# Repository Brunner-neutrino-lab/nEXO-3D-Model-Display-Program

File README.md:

# nEXO 3D Model and Display

## Overview

This project showcases a scaled-down, 3D-printed model of the nEXO detector, designed to visualize various data related to muon interactions and double beta decay events. The model is created using SolidWorks and powered by a Raspberry Pi, enabling interactive LED displays and simulated data visualization. This project aims to present condensed data from ten years of observation, highlighting the rarity of neutrino-less double beta decay.

## Table of Contents

1. [Introduction](#introduction)
2. [Project Features](#project-features)
3. [Responsibilities](#responsibilities)
4. [Hardware Components](#hardware-components)
5. [Software Components](#software-components)
6. [Setup and Installation](#setup-and-installation)
7. [Data Simulation](#data-simulation)
8. [Usage](#usage)
9. [Acknowledgments](#acknowledgments)

## Introduction

The nEXO detector is part of an experiment projected to detect neutrino-less double beta decay. Our project involves creating a scaled-down 3D model of the detector to visualize simulated muon data and rare decay events in an engaging and informative manner.

## Project Features

- **True-to-Scale 3D Model**: Created in SolidWorks, scaled down by a factor of 100, and optimized for 3D printing.
- **Simulated Data Visualization**:
  - Muons passing through the TPC (Time Projection Chamber).
  - Muons passing through the outer detector.
  - Coincident muons passing through both the TPC and outer detector.
  - Background Region of Interest (ROI) data.
  - Xenon 137 data.
  - Estimated rate of neutrino-less double beta decay.
- **Interactive LED Display**: Powered by a Raspberry Pi, the LED display will showcase multiple half-lives of the decay to highlight its rarity.
- **Condensed Time Frame**: Displaying ten years or five years of data in a two-minute or one-minute visualization respectively.

## Responsibilities

1. 3D model and printing
- Grace, Felix
2. Hardware
- Julien, Felix 
3. Programming
- Sophie, Emilio, Eliot

Brian is advising the programming and hardware

## Hardware Components

- Raspberry Pi (User: pi,  Pass: Element54$)
- 3D-printed model of the nEXO detector (32 components)
- LEDs (5 blue for walls and 4 blue for floor, RGB for TPC)
- Power supply
- Current-limiting resistors
- IC (transistors)
- HAT for raspberry pi
- Wires (mainly used 26AWG)
- Glue
- Mirror sheet

## Software Components

- SolidWorks for 3D modeling
- Python for controlling the Raspberry Pi and LEDs
- Data from previous simulation scripts for muon and decay events

## Setup and Installation

1. **3D Printing**:
   - Use the SolidWorks files provided in the [sharepoint](https://mcgill.sharepoint.com/:f:/s/BrunnerNeutrinoLabModels_Group/EvGFXZofQUZPt6qD_oMlr6YBIfcuM76ZlL9AQwnTyHu-Tg?e=94aHd1) to print the scaled-down model of the nEXO detector.
   
2. **Hardware Assembly**:
   - Schematics for the Raspberry Pi HAT and inside the model are found in the 'Schematics' folder.
   - Full tutorial on how to asssemble your own HAT found in 'nEXO Scale Model HAT text.docx'

4. **Software Installation**:
  - Assignment of GPIO pins for LEDS:
      - wallGPIO = 17 #physical/board pin 11
      - floorGPIO = 27 #physical/board pin 13
      - redGPIO = 9 #physical/board pin 21
      - greenGPIO = 11 #physical/board pin 23
      - blueGPIO = 25 #physical/board pin 22
  - The program to display the LEDs is found in the file 'LED_program.py'
  - 'Test.py' was only used to store the RGB values for the TPC colours.
      - in the 'Schematic' folder the LED colour assignment to events is found.

## Data Simulation
General approach: calculate the mean/expected time between events (for our time scale of 2 min = 10 years), then randomly sample the time between LED flashes using an exponential distribution (distribution for time between Poisson events). We have the option
 to vary the half-life of 0vbb as well as the LXe volume (inner 2t or inner 1t). 

The TPC will be flashed different colours for 5 different events in the ROI (the ROI is SS events, with energy within 0vbb FHWM): 
  - 0vbb
  - 2vbb
  - solar v
  - Xe-137 activations
  - and the remaining background events. 

0vbb: Mean number of decays per year is calculated based on the mean lifetime (half-life divided by log(2)), assuming 76.1% of events are in the ROI (as FHWM is approximately 76.1% of area under Gaussian distribution). 

  - 3 sigma discovery potential half-life: 7.4 x 10^27 years (https://iopscience.iop.org/article/10.1088/1361-6471/ac3631/pdf)   
  - Half-life sensitivity: 1.35 × 10^28 years
  - Our third option is currently 1 x 10^27 years.

Total background rate (https://arxiv.org/abs/1805.11142v2, table 3.1):  
  - Inner 2 tons: 3.6 × 10^−4 events/(FWHM·kg·yr)  
  - Inner 1 ton: 1.4 × 10^−4 events/(FWHM·kg·yr)  

Events in the background are separated into 2vbb, solar v, Xe-137 and remaining background according to the composition within FWHM for the inner 2t (https://iopscience.iop.org/article/10.1088/1361-6471/ac3631/pdf, estimated from Fig. 8):  
  - 2vbb: 0.8%  
  - Solar v: 2.1%  
  - Xe-137: 2.4%   
  - Rest of background: 94.7%  

The outer detector (walls and floor) will be flashed for muons (these rates may have to be scaled differently as they are very high with our time scale; currently the lights just stay on):  
  - Muons through TPC: about 0.6 per day 
  - Muons through outer cryostat: about 5 per day 

## Usage

1. **Start the Visualization**:
   - Run the main control script: GUI_program_with_LEDs.py
   - GUI will allow the user to choose options before running simulation

2. **Interacting with the Model**:
   - The LEDs will display different data sets including muons, 2vbb, 0vbb, ROI background data, and Xenon 137 data.
   - There will be an option to view the data from the inner 1 tonne as well as the inner 2 tonne of the detector.
   - Observe the visualization of the estimated rate of neutrino-less double beta decay and its half-lives.
3. **Connecting over SSH**
   - pi must be connected to the same network as device (ethernet/internet)
   - type into terminal 'ssh pi@[pi IP address]'
   - if displaying on touchscreeen you have to define the display enviroment (the screen is just DISPLAY=:0) before the command
     - ex. DISPLAY=:0 gui.py
     - ex. sudo DISPLAY=:0 LEDs.py

## Acknowledgments

This project is developed for the nEXO collaboration's Director's Review.
For questions contact Grace at grace.champagne@mail.mcgill.ca

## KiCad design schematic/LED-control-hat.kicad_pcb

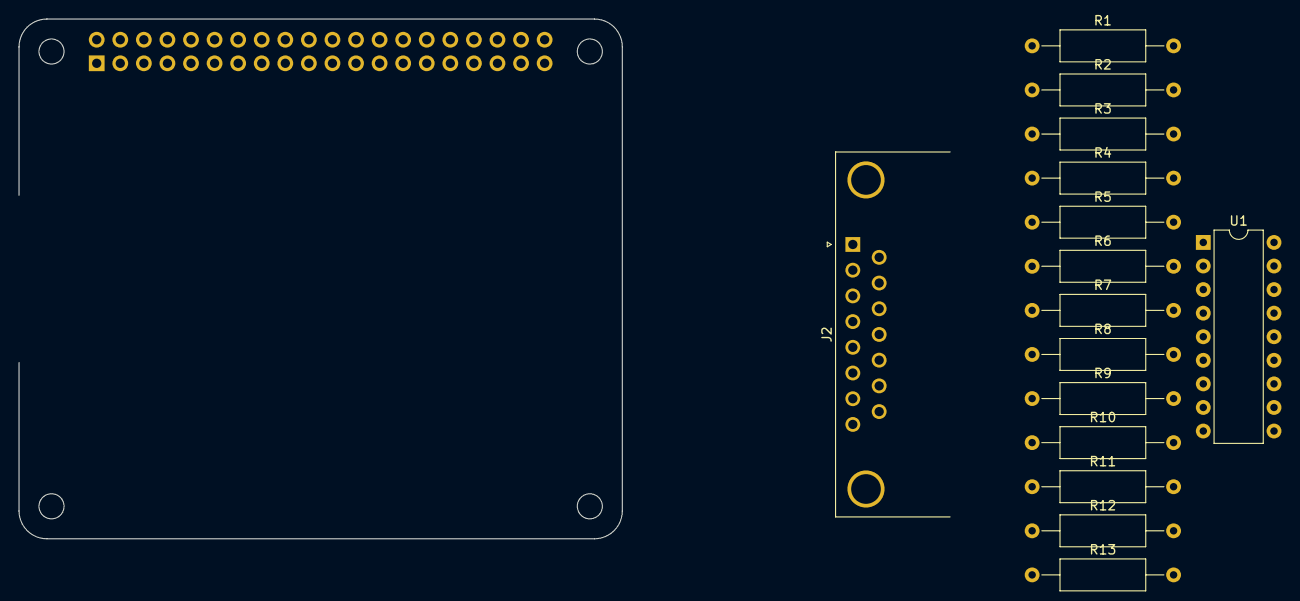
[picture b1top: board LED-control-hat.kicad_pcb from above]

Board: 2 copper layers, 65.0 x 56.0 mm, 20 parts (1 on the bottom side), 26 nets, no tracks yet.

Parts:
J1: GPIO; PinSocket_2x20_P2.54mm_Vertical
J2: DA15_Receptacle; DSUB-15_Female_Horizontal_P2.77x2.84mm_EdgePinOffset7.70mm_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
MH1, MH2, MH3, MH4: MountingHole_2.7mm_M2.5
R1, R2, R3, R4, R5, R6, R7, R8, R9, R10, R11, R12, R13: R_US; R_Axial_DIN0309_L9.0mm_D3.2mm_P15.24mm_Horizontal
U1: ULN2803A; DIP-18_W7.62mm

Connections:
+3V3: J1.1, J1.17
+5V: J1.2, J1.4, J2.1
/GPIO17: J1.11, U1.1 (I1)
/GPIO22: J1.15, U1.2 (I2)
/GPIO23: J1.16, U1.3 (I3)
/GPIO24: J1.18, U1.4 (I4)
/GPIO25: J1.22, U1.5 (I5)
GND: J1.6, J1.9, J1.14, J1.20, J1.25, J1.30, J1.34, J1.39, U1.9 (GND)
unnamed: J2.9, R1.2
unnamed: J2.10, R3.2
unnamed: J2.12, R7.2
unnamed: J2.13, R9.2
unnamed: J2.14, R11.2
unnamed: J2.15, R13.2
unnamed: J2.11 (P111), R5.2
unnamed: J2.2, R2.2
unnamed: J2.3, R4.2
unnamed: J2.4, R6.2
unnamed: J2.5, R8.2
unnamed: J2.6, R10.2
unnamed: J2.7, R12.2
unnamed: R1.1, U1.18 (O1)
unnamed: R2.1, U1.17 (O2)
unnamed: R3.1, U1.16 (O3)
unnamed: R4.1, R5.1, R6.1, R7.1, R8.1, U1.15 (O4)
unnamed: R9.1, R10.1, R11.1, R12.1, R13.1, U1.14 (O5)

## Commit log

2024-06-10 Create 2024-06-10.md
    meeting minutes for first meeting
2024-06-11 Create 2024-05-17.md
    layout for meeting 2
2024-06-17 LED draft code
    to test if LED's turn on through GPIO pins with expected resistor values
2024-06-20 Create screenshot
2024-06-20 kicad
    all kicad files for HAT circuit and inside model connections
2024-06-20 screenshot
2024-06-20 LED colour assignments
2024-06-25 Create to_do.md
    to do list as well as completed tasks
2024-06-26 changes to LED colours
2024-06-26 changed GPIO.cleanup location
2024-07-02 files for GUI on touchscreen
2024-07-08 Delete 3d model code for gui.py
    downloading new one with comments
2024-07-08 GUI program with LEDs with comments
2024-07-08 Update GUI program with LEDs.py
    no more tkvideo
2024-07-08 Update GUI program with LEDs.py
    uncommented GPIO parts
2024-07-08 Update GUI program with LEDs.py
    made font smaller
2024-07-10 Create schematic
2024-07-10 Screenshots of Schematic
2024-07-11 Update GUI program with LEDs.py
    stop works?
2024-07-12 Create log.txt
    for when program starts at boot
2024-07-12 changes so that will start at boot
2024-07-12 getting red of useless files
2024-07-12 Update GUI program with LEDs.py
    added option to stop simulation
2024-10-25 Update README.md
    added info on what is nEXO Scale Model HAT text.docx
2024-10-25 Update README.md
    added information for contact
2024-11-08 Create test_rgb
    to test the rgb led for red, green and blue
